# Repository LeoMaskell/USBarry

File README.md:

# USBarry

USBarry is a USB-stick style hardware project built for technology prototyping and Git-connected workflows, with a strong privacy-focused design philosophy.

## Overview

This repository contains the design files and notes for the USBarry hardware project, including PCB and CAD assets, with an emphasis on privacy-conscious hardware development.

## Repository Structure

- `PCB/` – PCB design files
- `CAD/` – CAD and mechanical design assets
- `BOM.txt` – Bill of materials
- `notes.md` / `notes.txt` – Project notes

## Project Images

### Hardware Render

### PCB / Layout View

### Additional Board View

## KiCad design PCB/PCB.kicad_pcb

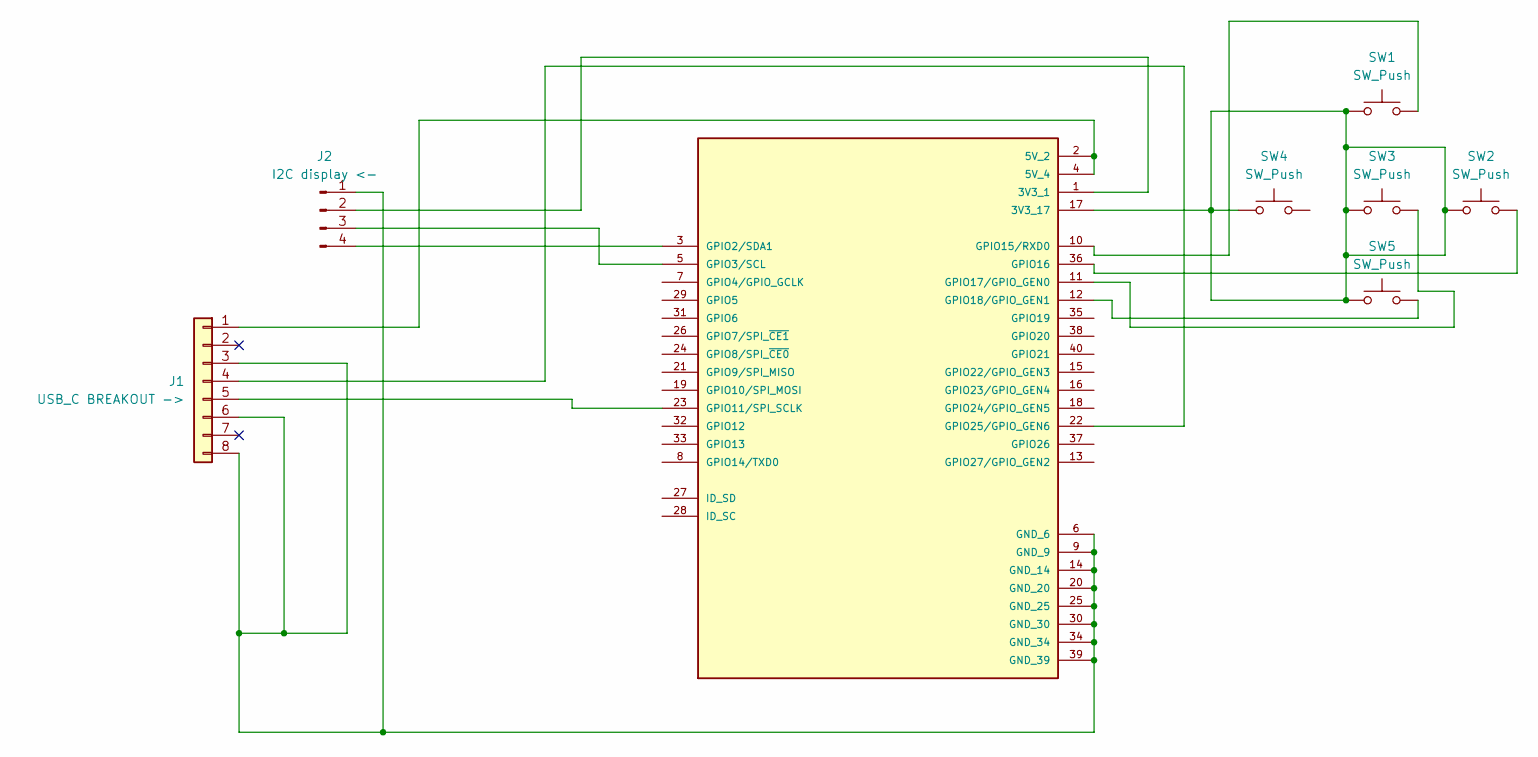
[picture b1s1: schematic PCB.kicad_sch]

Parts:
J1: USB_C BREAKOUT ->; PinHeader_1x08_P2.54mm_Vertical
J2: I2C display <-; PinHeader_1x04_P2.54mm_Vertical
SW1, SW2, SW3, SW4, SW5: SW_Push; SW_SPST_Omron_B3F-40xx
U1: RASPBERRY_PI_ZERO_2_W; MODULE_RASPBERRY_PI_ZERO_2_W; PARTREV April 2024

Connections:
unnamed: J1.1, U1.2 (5V_2), U1.4 (5V_4)
unnamed: J1.3, J1.6, J1.8, J2.1, U1.6 (GND_6), U1.9 (GND_9), U1.14 (GND_14), U1.20 (GND_20), U1.25 (GND_25), U1.30 (GND_30), U1.34 (GND_34), U1.39 (GND_39)
unnamed: J1.4, U1.22 (GPIO25/GPIO_GEN6)
unnamed: J1.5, U1.23 (GPIO11/SPI_SCLK)
unnamed: J2.2, U1.1 (3V3_1)
unnamed: J2.3, U1.5 (GPIO3/SCL)
unnamed: J2.4, U1.3 (GPIO2/SDA1)
unnamed: SW1.1, SW2.1, SW3.1, SW4.1 (1_1), SW5.1, U1.17 (3V3_17)
unnamed: SW1.2, U1.10 (GPIO15/RXD0)
unnamed: SW2.2, U1.36 (GPIO16)
unnamed: SW3.2, U1.11 (GPIO17/GPIO_GEN0)
unnamed: SW5.2, U1.12 (GPIO18/GPIO_GEN1)

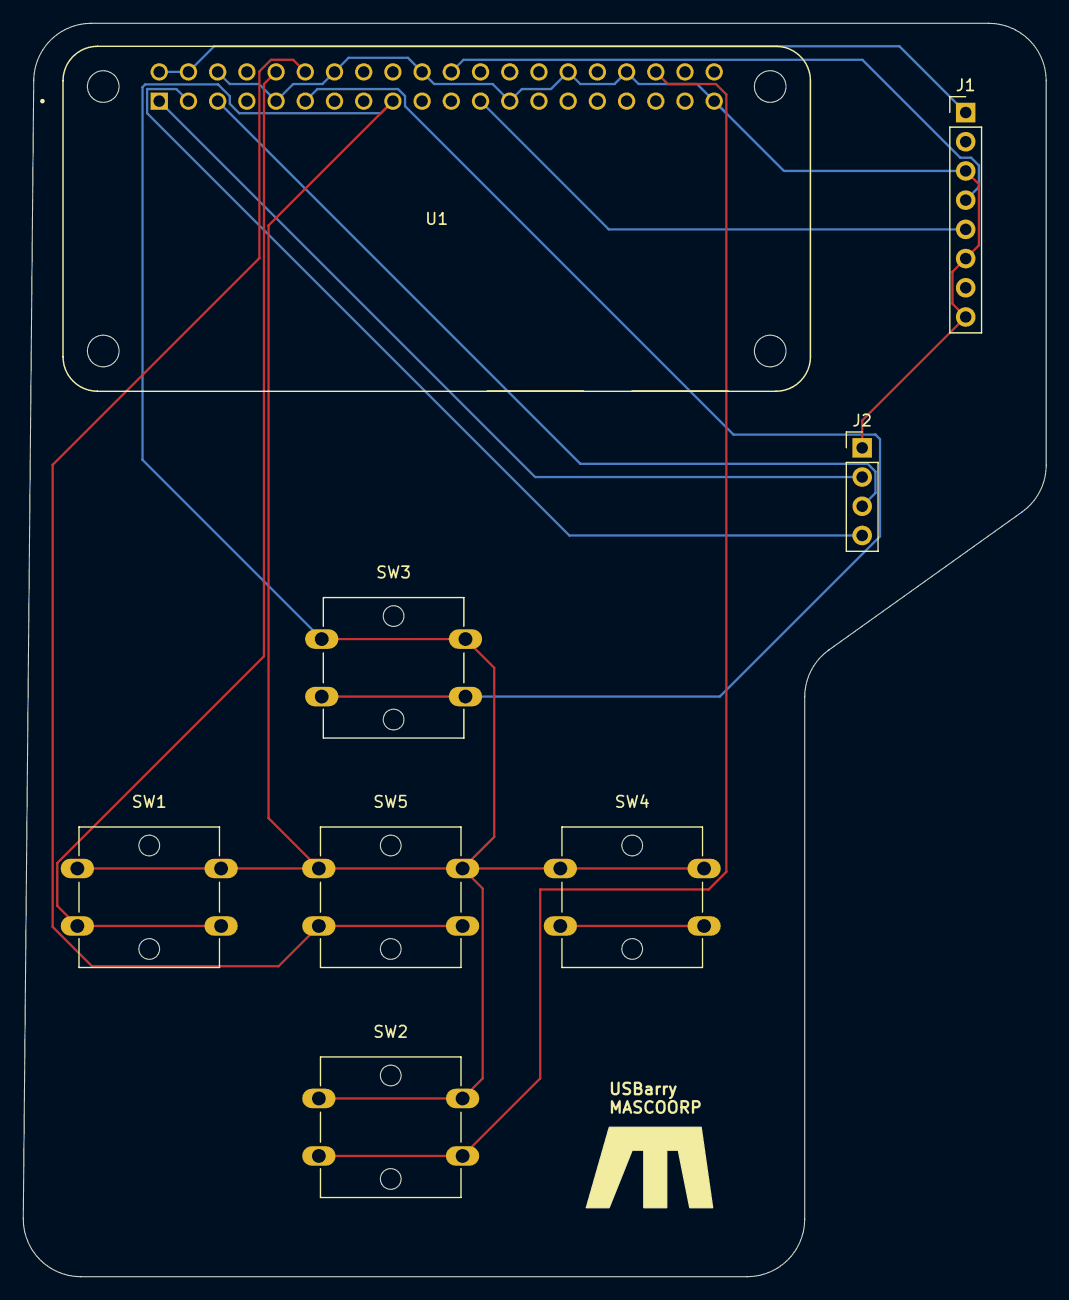
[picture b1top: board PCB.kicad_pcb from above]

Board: 2 copper layers, 89.0 x 109.0 mm, 8 parts (0 on the bottom side), 12 nets.

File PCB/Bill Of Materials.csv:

"Reference","Qty","Value","DNP","Exclude from BOM","Exclude from Board","Footprint","Datasheet"
"J1","1","USB_C BREAKOUT ->","","","","Connector_PinHeader_2.54mm:PinHeader_1x08_P2.54mm_Vertical",""
"J2","1","I2C display <-","","","","Connector_PinHeader_2.54mm:PinHeader_1x04_P2.54mm_Vertical",""
"SW1,SW2,SW3,SW4,SW5","5","SW_Push","","","","Button_Switch_THT:SW_SPST_Omron_B3F-40xx",""
"U1","1","RASPBERRY_PI_ZERO_2_W","","","","RASPBERRY_PI_ZERO_2_W:MODULE_RASPBERRY_PI_ZERO_2_W",""

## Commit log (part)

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2026-06-10 added notes.txt
2026-06-20 sorting the PCB
2026-06-21 finnished PCB and did a notes.md
2026-06-28 added the brand silkscreeen
2026-06-29 rewired
